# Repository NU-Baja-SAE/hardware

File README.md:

# NU Baja SAE — Hardware

KiCad schematics, PCB layouts, wiring harness designs, and BOM tooling for all NU Baja SAE electronics boards: the eCVT controller, the DAQ node, and the HUD node.

This guide assumes you have never used Git, GitHub, or KiCad before. Follow it top to bottom the first time; after that, skip to [Day-to-day workflow](#day-to-day-workflow).

## Table of contents

- [Glossary](#glossary)
- [One-time setup](#one-time-setup)
- [Getting the files onto your computer](#getting-the-files-onto-your-computer)
- [Opening a board in KiCad](#opening-a-board-in-kicad)
- [Day-to-day workflow](#day-to-day-workflow)
- [Structure](#structure)
- [Releases](#releases)
- [KiCad version](#kicad-version)

## Glossary

A few words you will see everywhere in this guide and on GitHub itself:

| Term | Meaning |
|---|---|
| Repository ("repo") | A folder of files (this one) tracked by Git, with full history of every change. |
| Git | The tool that tracks changes to files over time. Runs on your computer. |
| GitHub | The website that hosts a copy of the repo online so the team can share it. |
| Clone | Downloading a full copy of the repo (with its history) onto your computer. |
| Commit | A saved snapshot of your changes, with a short message describing what changed. |
| Push | Uploading your commits from your computer to GitHub. |
| Pull | Downloading other people's commits from GitHub to your computer. |
| Branch | An independent line of work, so you can make changes without touching `main` until they are ready. |
| Pull Request (PR) | A request to merge your branch into `main`, where others can review your changes before they land. |
| `main` | The default branch — the official, current state of the repo. |

## One-time setup

You only need to do this once per computer.

1. Create a GitHub account at [github.com](https://github.com) if you do not have one, and ask a team lead to add you to the `NU-Baja-SAE` organization so you have push access.
2. Install Git:
   - Windows: download and run the installer from [git-scm.com](https://git-scm.com/downloads). Default options are fine.
   - Mac: open Terminal and run `git --version` — macOS will offer to install it for you if it is missing.
3. Install GitHub Desktop (recommended if you are new to Git) from [desktop.github.com](https://desktop.github.com). It gives you a visual interface for the commit/push/pull steps below instead of typing commands. Everything in this guide can be done either with GitHub Desktop's buttons or with the `git` command line — both are described below.
4. Install KiCad — see [KiCad version](#kicad-version) below for which version to install. Download from [kicad.org/download](https://www.kicad.org/download/).
5. After cloning the repo (next section), add the shared parts library so connectors/ICs used across boards show up in KiCad — see [`libraries/README.md`](libraries/README.md).

## Getting the files onto your computer

This is called cloning the repo — it only needs to be done once per computer, after which you just "pull" updates.

Using GitHub Desktop:
1. Open GitHub Desktop and sign in with your GitHub account (File → Options → Accounts).
2. Click File → Clone Repository.
3. Choose the URL tab and paste: `https://github.com/NU-Baja-SAE/hardware`
4. Pick a local folder (e.g. `Documents/NU-Baja-SAE/hardware`) and click Clone.

Using the command line (Git Bash on Windows, Terminal on Mac):
```
git clone https://github.com/NU-Baja-SAE/hardware.git
cd hardware
```

Either way, you now have a folder called `hardware` on your computer containing everything in this repo.

## Opening a board in KiCad

Each board lives in its own folder under `boards/`, e.g. `boards/ecvt-controller/`. Inside that folder is a `.kicad_pro` file — this is the project file.

1. Open KiCad.
2. File → Open Project, then navigate to e.g. `hardware/boards/ecvt-controller/` and select the `.kicad_pro` file.
3. KiCad's project window shows the schematic (`.kicad_sch`) and PCB layout (`.kicad_pcb`) for that board — double-click either to open it in the schematic editor or PCB editor.
4. Make your edits and save (Ctrl+S / Cmd+S) as you normally would in KiCad. Saving only writes to your local copy of the files — it does not upload anything to GitHub. See the next section for how to share your changes.

If you are new to KiCad itself (not just this repo), the official [Getting Started guide](https://docs.kicad.org/) walks through schematic capture and PCB layout basics — worth a read before your first board edit.

## Day-to-day workflow

The general loop, every time you sit down to work on a board:

### 1. Pull the latest changes

Before you start editing, make sure you have everyone else's latest work, so you are not editing an outdated copy.

- GitHub Desktop: click Fetch origin, then Pull origin if it appears.
- Command line: `git pull`

### 2. Create a branch for your change

Do not edit `main` directly — work on a branch so your in-progress changes do not affect anyone else until they are reviewed.

- GitHub Desktop: click the branch dropdown (top middle) → New Branch. Name it something descriptive, e.g. `ecvt-add-current-sense`.
- Command line: `git checkout -b ecvt-add-current-sense`

### 3. Make your changes

Edit the KiCad files (schematic, PCB, etc.), or BOM/harness files, and save them as usual.

### 4. Commit your changes

A commit is a saved checkpoint with a message describing what you did. Commit often, in small logical chunks (e.g. "Add current sense resistor to eCVT controller" rather than one giant commit at the end).

- GitHub Desktop: the left panel lists every changed file. Check the ones you want to include, write a summary in the box at bottom-left, and click Commit to `<branch-name>`.
- Command line:
  ```
  git add boards/ecvt-controller/
  git commit -m "Add current sense resistor to eCVT controller"
  ```

### 5. Push your branch to GitHub

This uploads your commits so others (and CI, see below) can see them.

- GitHub Desktop: click Push origin.
- Command line: `git push -u origin ecvt-add-current-sense`

### 6. Open a Pull Request (PR)

A PR is how you propose merging your branch into `main`.

1. Go to [github.com/NU-Baja-SAE/hardware](https://github.com/NU-Baja-SAE/hardware) — GitHub usually shows a yellow banner offering to Compare & pull request for the branch you just pushed. Click it (or use GitHub Desktop's Create Pull Request button).
2. Write a short description of what changed and why.
3. Click Create pull request.
4. Automated checks (CI) will run against your PR — see `.github/workflows/ci.yml` for what gets checked (ERC/DRC, BOM diff, rendered schematic/PCB images, etc.). Wait for these to finish and fix anything they flag.
5. Ask a teammate to review. Once approved, click Merge pull request on GitHub.
6. Delete the branch (GitHub will prompt you) — its changes now live permanently in `main`.

### 7. Switch back to `main` and pull

- GitHub Desktop: switch the branch dropdown back to `main`, then Pull origin.
- Command line: `git checkout main && git pull`

You are back to a clean, up-to-date `main`, ready to start the loop again for your next change.

## Structure

```
hardware/
├── boards/
│   ├── ecvt-controller/   (.kicad_pro/.kicad_sch/.kicad_pcb + fab-outputs/ + README.md)
│   ├── daq-node/
│   └── hud-node/
├── harness/                # WireViz or WireLab YAML source + output/ (generated SVGs)
├── bom/
│   ├── consolidated-bom.csv
│   └── scripts/generate_bom.py
├── libraries/              # shared KiCad symbol/footprint libs
└── .github/workflows/
```

- `boards/<name>/` — one folder per physical board. Each contains its own KiCad project (`.kicad_pro`), schematic (`.kicad_sch`), PCB layout (`.kicad_pcb`), a `fab-outputs/` folder for generated gerbers/drill files/STEP models (not committed by hand — see below), and a short `README.md` describing the board.
- `harness/` — wiring harness definitions (WireViz/WireLab YAML), with rendered diagrams in `harness/output/`.
- `bom/` — the consolidated bill of materials across all boards (`consolidated-bom.csv`), generated automatically from the schematics by `bom/scripts/generate_bom.py`. Never edit the CSV by hand. If you change a schematic, run `python3 bom/scripts/generate_bom.py` and commit the updated CSV alongside your change — CI fails the PR if the committed CSV is out of date (and auto-regenerates it on direct pushes to `main` as a safety net).
- `libraries/` — shared KiCad symbol and footprint libraries used by more than one board, so parts stay consistent across designs.
- `.github/workflows/` — CI configuration; this is what automatically checks your PRs (see step 6 above).

Do not manually commit fab outputs (gerbers, drill files, `.step` files) — these are generated from the KiCad source files and are gitignored. CI regenerates them automatically on each PR.

## Releases

Board releases are tagged at the point gerbers are sent to fab, e.g. `ecvt-controller-v1.2`, with a one-line changelog per board.

## KiCad version

All board files must be authored/saved in the same KiCad version to avoid spurious diffs from format upgrades. Current standard version: **KiCad 10.0** — this is also the version CI runs (the `kicad/kicad:10.0` image in `.github/workflows/ci.yml`), so files saved in a newer major version will fail CI until both are bumped together.

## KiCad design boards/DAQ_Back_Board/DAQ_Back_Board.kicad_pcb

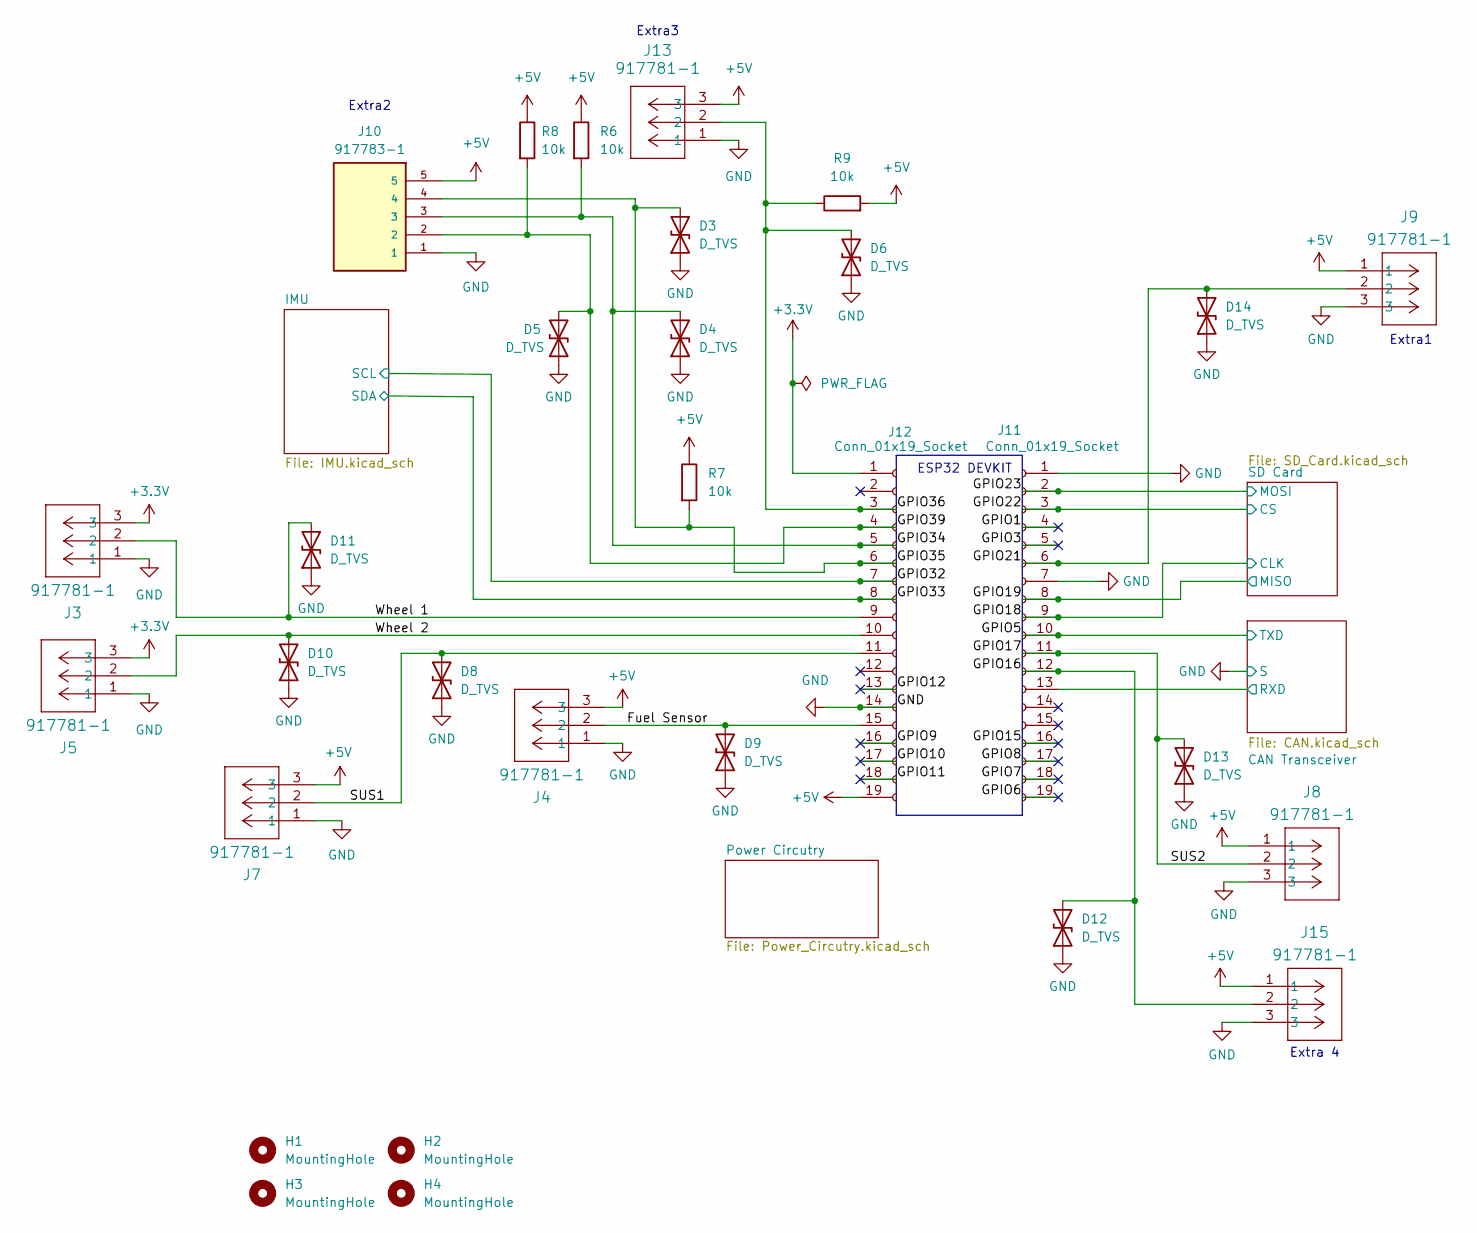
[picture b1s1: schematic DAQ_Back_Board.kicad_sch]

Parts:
D3, D4, D5, D6, D8, D9, D10, D11, D12, D13, D14: D_TVS; D_SOD-323_HandSoldering
H1, H2, H3, H4: MountingHole; MountingHole_3.2mm_M3
J3, J4, J5, J7, J8, J9, J13, J15: 917781-1; TE-Connectivity_917781
J10: 917783-1; Connector_1x5; PARTREV R
J11, J12: Conn_01x19_Socket; PinSocket_1x19_P2.54mm_Vertical
R6, R7, R8, R9: 10k; R_0603_1608Metric_Pad0.98x0.95mm_HandSolder

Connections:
+3.3V: J3.3, J5.3, J12.1; also elsewhere on the board
+5V: J4.3, J7.3, J8.1, J9.1, J10.5, J12.19, J13.3, J15.1, R6.1, R7.1, R8.1, R9.2; also elsewhere on the board
/CAN Transceiver/RXD: J11.13; also elsewhere on the board
/Fuel Sensor: D9.2 (A2), J4.2, J12.15
/GPIO1: J11.4
/GPIO3: J11.5
/GPIO5: J11.10; also elsewhere on the board
/GPIO6: J11.19
/GPIO7: J11.18
/GPIO8: J11.17
/GPIO9: J12.16
/GPIO10: J12.17
/GPIO11: J12.18
/GPIO12: J12.13
/GPIO15: J11.16
/GPIO16: D12.2 (A2), J11.12, J15.2
/GPIO17: D13.2 (A2), J8.2, J11.11
/GPIO18: J11.9; also elsewhere on the board
/GPIO19: J11.8; also elsewhere on the board
/GPIO21: D14.2 (A2), J9.2, J11.6
/GPIO22: J11.3; also elsewhere on the board
/GPIO23: J11.2; also elsewhere on the board
/GPIO32: J12.7; also elsewhere on the board
/GPIO33: J12.8; also elsewhere on the board
/GPIO34: D4.2 (A2), J10.3, J12.5, R6.2
/GPIO35: D3.2 (A2), J10.4, J12.6, R7.2
/GPIO36: D6.2 (A2), J12.3, J13.2, R9.1
/GPIO39: D5.2 (A2), J10.2, J12.4, R8.2
/SUS1: D8.2 (A2), J7.2, J12.11
/Wheel 1: D11.2 (A2), J3.2, J12.9
/Wheel 2: D10.2 (A2), J5.2, J12.10
GND: D3.1 (A1), D4.1 (A1), D5.1 (A1), D6.1 (A1), D8.1 (A1), D9.1 (A1), D10.1 (A1), D11.1 (A1), D12.1 (A1), D13.1 (A1), D14.1 (A1), J3.1, J4.1, J5.1, J7.1, J8.3, J9.3, J10.1, J11.1, J11.7, J12.14, J13.1, J15.3; also elsewhere on the board

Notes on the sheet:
ESP32 DEVKIT
Extra2
Extra1
Extra3
Extra 4

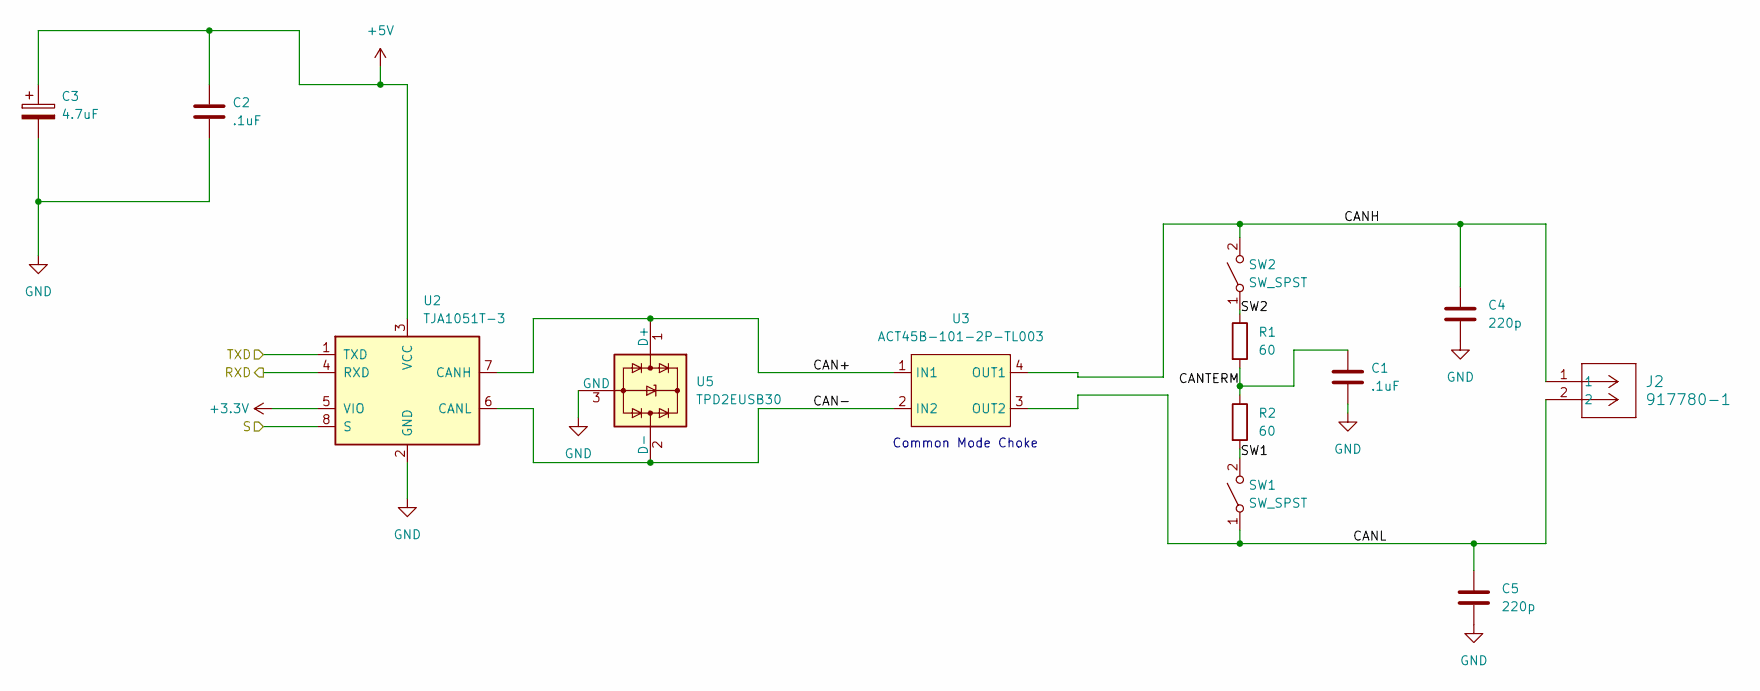
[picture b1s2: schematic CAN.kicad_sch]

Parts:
C1, C2: .1uF; C_0603_1608Metric_Pad1.08x0.95mm_HandSolder
C3: 4.7uF; C_0603_1608Metric_Pad1.08x0.95mm_HandSolder
C4, C5: 220p; C_0603_1608Metric_Pad1.08x0.95mm_HandSolder
J2: 917780-1; TE-Connectivity_ 917780
R1, R2: 60; R_1206_3216Metric_Pad1.30x1.75mm_HandSolder
SW1, SW2: SW_SPST; SW_DIP_SPSTx01_Slide_Copal_CHS-01A_W5.08mm_P1.27mm_JPin
U2: TJA1051T-3; SOIC-8_3.9x4.9mm_P1.27mm
U3: ACT45B-101-2P-TL003
U5: TPD2EUSB30; Texas_DRT-3

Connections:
+3.3V: U2.5 (VIO); also elsewhere on the board
+5V: C2.1, C3.1, U2.3 (VCC); also elsewhere on the board
/CAN Transceiver/CAN+: U2.7 (CANH), U3.1 (IN1), U5.1 (D+)
/CAN Transceiver/CAN-: U2.6 (CANL), U3.2 (IN2), U5.2 (D-)
/CAN Transceiver/CANH: C4.1, J2.1, SW2.2 (B), U3.4 (OUT1)
/CAN Transceiver/CANL: C5.1, J2.2, SW1.1 (A), U3.3 (OUT2)
/CAN Transceiver/CANTERM: C1.1, R1.2, R2.1
/CAN Transceiver/RXD: U2.4 (RXD); also elsewhere on the board
/CAN Transceiver/SW1: R2.2, SW1.2 (B)
/CAN Transceiver/SW2: R1.1, SW2.1 (A)
/GPIO5: U2.1 (TXD); also elsewhere on the board
GND: C1.2, C2.2, C3.2, C4.2, C5.2, U2.2 (GND), U2.8 (S), U5.3 (GND); also elsewhere on the board

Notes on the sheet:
Common Mode Choke

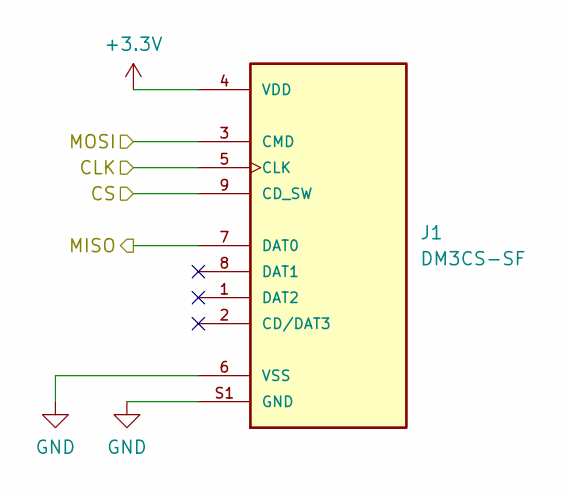
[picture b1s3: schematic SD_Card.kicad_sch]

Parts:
J1: DM3CS-SF; SD_Card; PARTREV n/a

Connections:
+3.3V: J1.4 (VDD); also elsewhere on the board
/GPIO18: J1.5 (CLK); also elsewhere on the board
/GPIO19: J1.7 (DAT0); also elsewhere on the board
/GPIO22: J1.9 (CD_SW); also elsewhere on the board
/GPIO23: J1.3 (CMD); also elsewhere on the board
GND: J1.6 (VSS), J1.S1 (GND), J1.S2 (GND), J1.S3 (GND), J1.S5 (GND); also elsewhere on the board

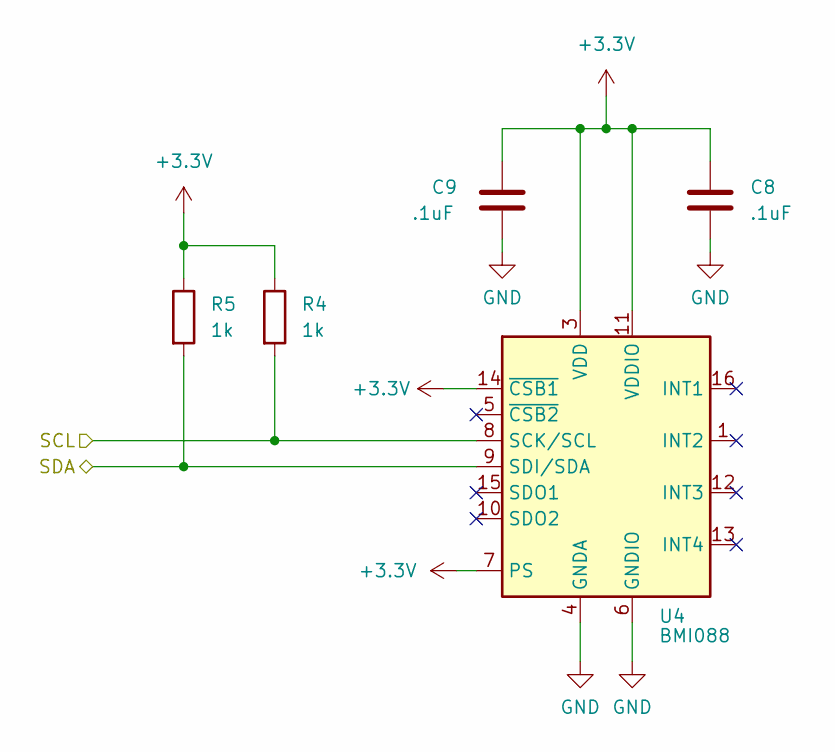
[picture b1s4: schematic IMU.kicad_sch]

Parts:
C8, C9: .1uF; C_0603_1608Metric_Pad1.08x0.95mm_HandSolder
R4, R5: 1k; R_0603_1608Metric_Pad0.98x0.95mm_HandSolder
U4: BMI088; Bosch_LGA-16_4.5x3mm_P0.5mm_LayoutBorder7x1y_ClockwisePinNu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

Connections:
+3.3V: C8.1, C9.1, R4.1, R5.1, U4.3 (VDD), U4.7 (PS), U4.11 (VDDIO), U4.14 (~CSB1); also elsewhere on the board
/GPIO32: R4.2, U4.8 (SCK/SCL); also elsewhere on the board
/GPIO33: R5.2, U4.9 (SDI/SDA); also elsewhere on the board
GND: C8.2, C9.2, U4.2 (GNDA), U4.4 (GNDA), U4.6 (GNDIO); also elsewhere on the board

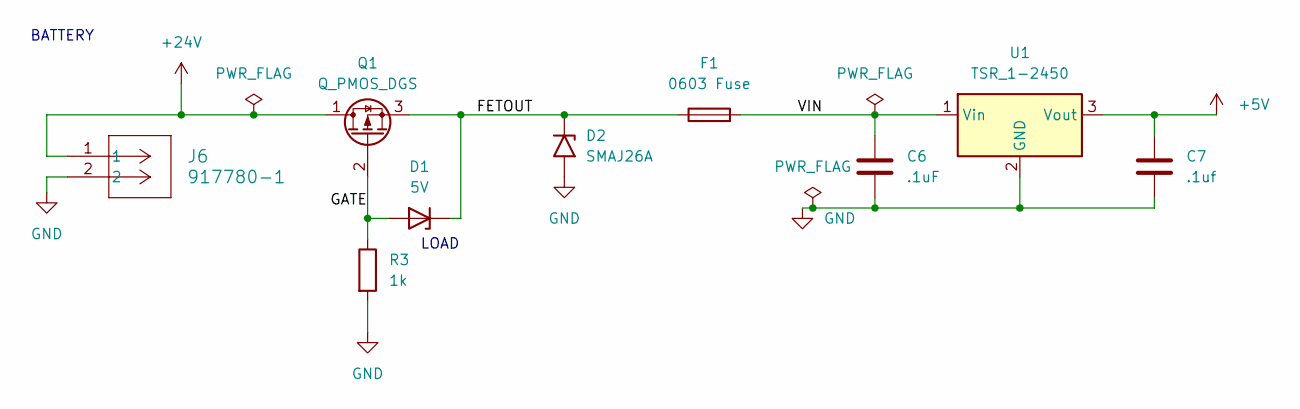
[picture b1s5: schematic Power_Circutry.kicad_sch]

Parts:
C6: .1uF; C_0603_1608Metric_Pad1.08x0.95mm_HandSolder
C7: .1uf; C_0603_1608Metric_Pad1.08x0.95mm_HandSolder
D1: 5V; D_SMA
D2: SMAJ26A; D_SMA
F1: 0603 Fuse; Fuse_0603_1608Metric_Pad1.05x0.95mm_HandSolder
J6: 917780-1; TE-Connectivity_ 917780
Q1: Q_PMOS_DGS; SOT-23-3
R3: 1k; R_0603_1608Metric_Pad0.98x0.95mm_HandSolder
U1: TSR_1-2450; Converter_DCDC_TRACO_TSR-1_THT

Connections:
+5V: C7.1, U1.3 (Vout); also elsewhere on the board
+24V: J6.1, Q1.1 (D)
/Power Circutry/FETOUT: D1.1 (K), D2.1 (A1), F1.1, Q1.3 (S)
/Power Circutry/GATE: D1.2 (A), Q1.2 (G), R3.1
/Power Circutry/VIN: C6.1, F1.2, U1.1 (Vin)
GND: C6.2, C7.2, D2.2 (A2), J6.2, R3.2, U1.2 (GND); also elsewhere on the board

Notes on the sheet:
LOAD
BATTERY

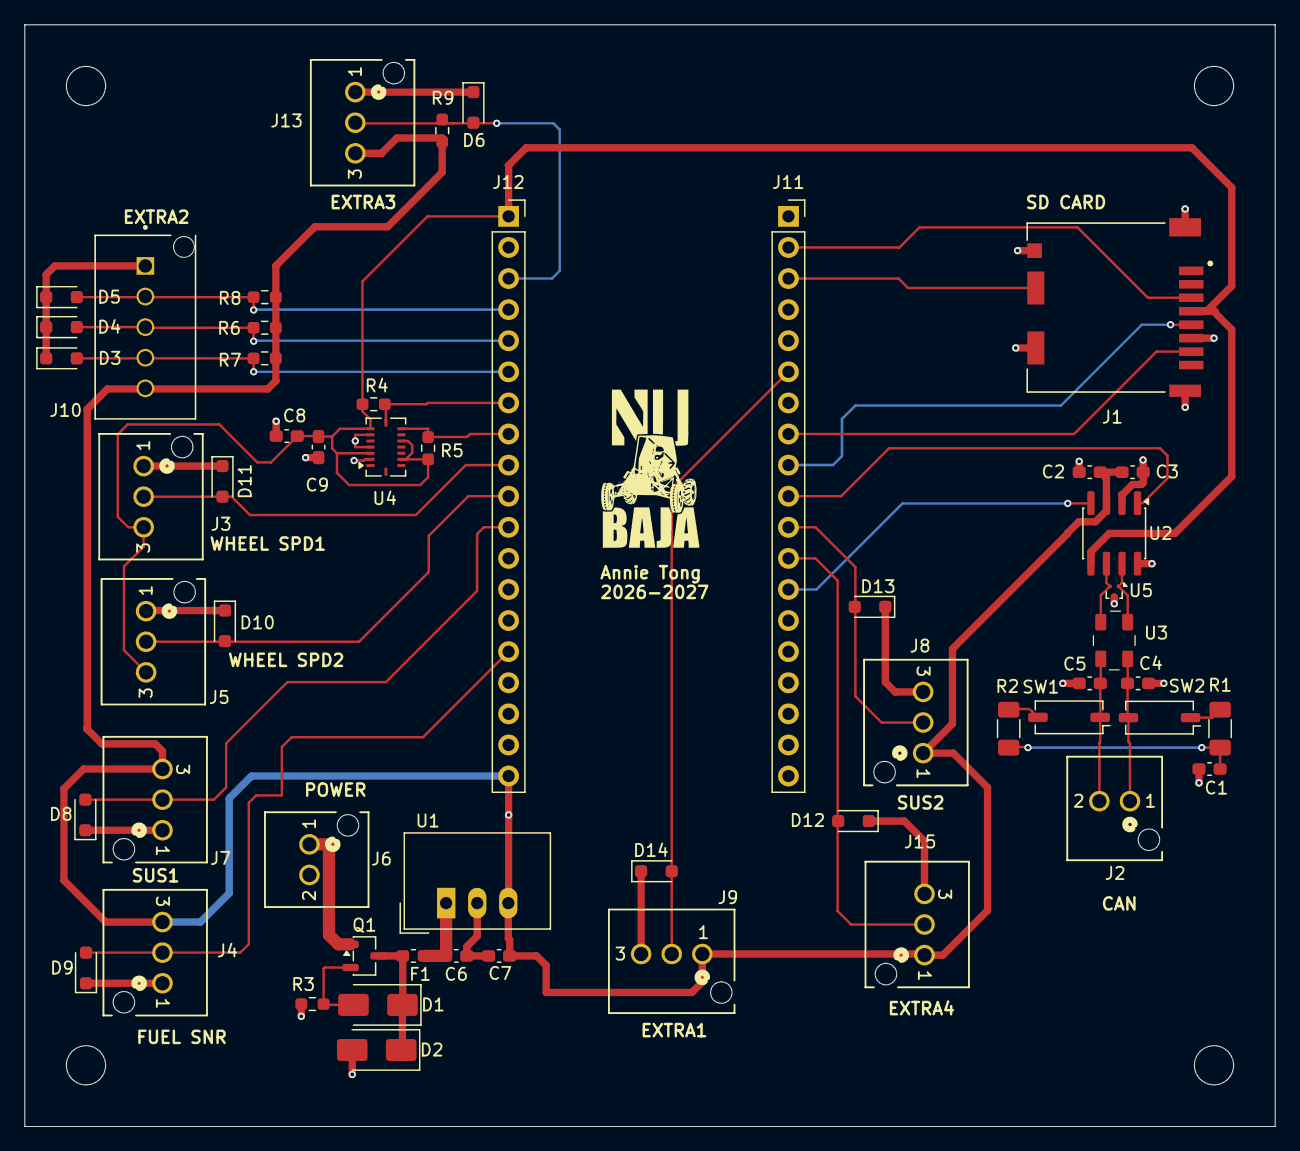
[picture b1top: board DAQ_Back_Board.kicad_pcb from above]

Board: 4 copper layers, 102.2 x 90.0 mm, 58 parts (0 on the bottom side), 33 nets.

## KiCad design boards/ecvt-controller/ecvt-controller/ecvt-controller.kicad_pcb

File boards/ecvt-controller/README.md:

# ecvt-controller

KiCad project for the eCVT controller board. Add `.kicad_pro`/`.kicad_sch`/`.kicad_pcb` files here, with generated fab outputs under `fab-outputs/` (gitignored).

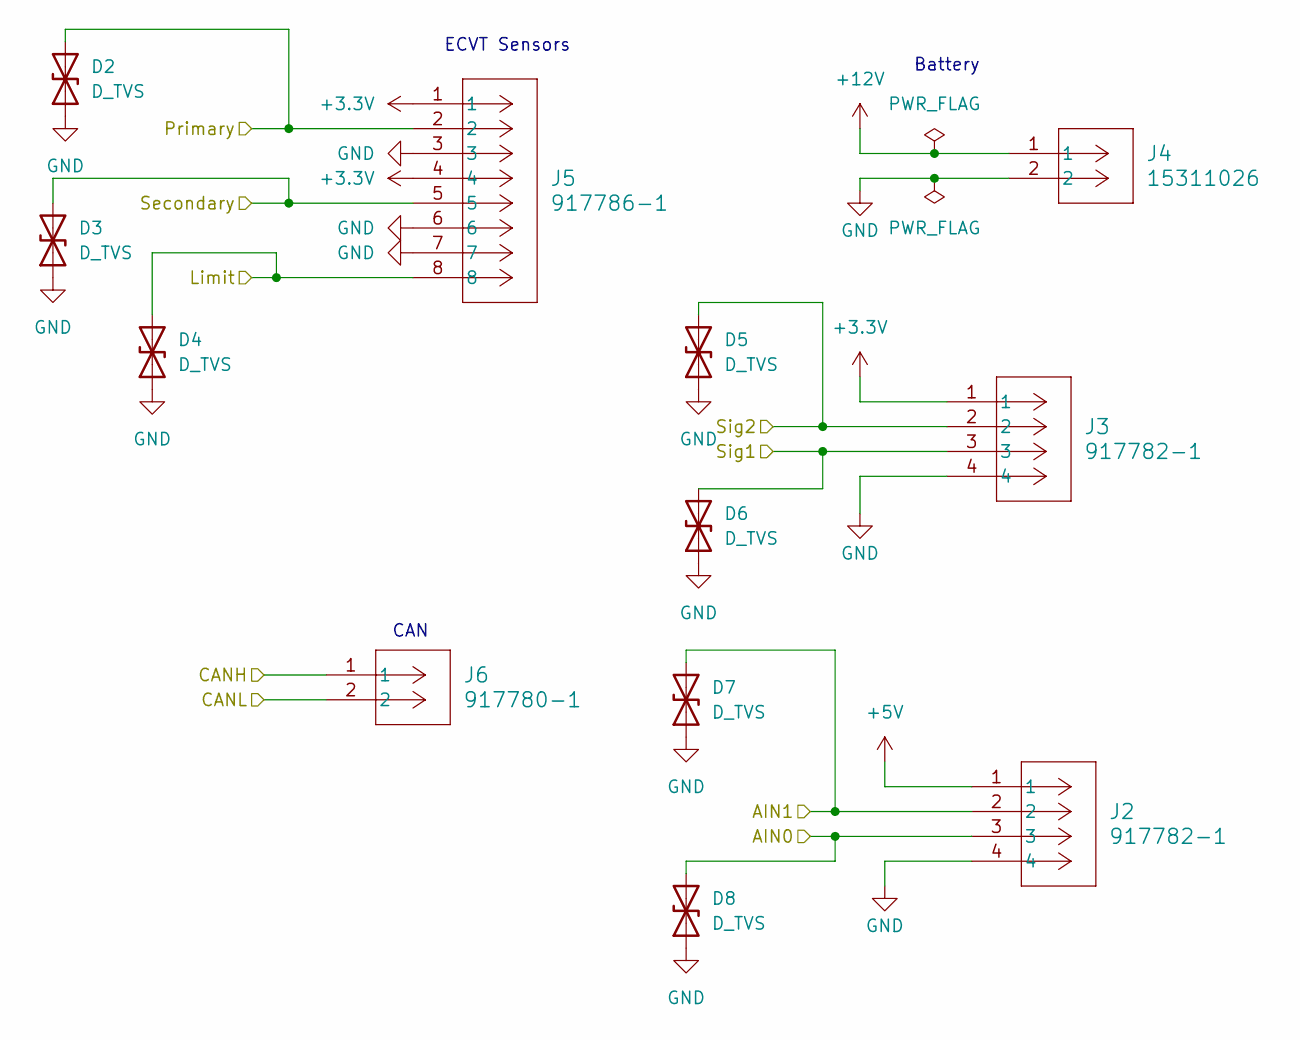
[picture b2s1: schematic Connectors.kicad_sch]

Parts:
D2, D3, D4, D5, D6, D7, D8: D_TVS; D_SOD-323_HandSoldering
J2, J3: 917782-1; CON4_1X4_P100
J4: 15311026; MOLEX_15311026
J5: 917786-1; TE-Connectivity_917786
J6: 917780-1; TE-Connectivity_ 917780

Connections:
+5V: J2.1; also elsewhere on the board
+12V: J4.1; also elsewhere on the board
/ADC/AIN0: D8.2 (A2), J2.3; also elsewhere on the board
/ADC/AIN1: D7.2 (A2), J2.2; also elsewhere on the board
/CAN/CANH: J6.1; also elsewhere on the board
/CAN/CANL: J6.2; also elsewhere on the board
/Connectors/Limit: D4.2 (A2), J5.8; also elsewhere on the board
/Connectors/Primary: D2.2 (A2), J5.2; also elsewhere on the board
/Connectors/Secondary: D3.2 (A2), J5.5; also elsewhere on the board
/Connectors/Sig1: D6.2 (A2), J3.3; also elsewhere on the board
/Connectors/Sig2: D5.2 (A2), J3.2; also elsewhere on the board
GND: D2.1 (A1), D3.1 (A1), D4.1 (A1), D5.1 (A1), D6.1 (A1), D7.1 (A1), D8.1 (A1), J2.4, J3.4, J4.2, J5.3, J5.6, J5.7; also elsewhere on the board

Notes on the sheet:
ECVT Sensors
CAN
Battery

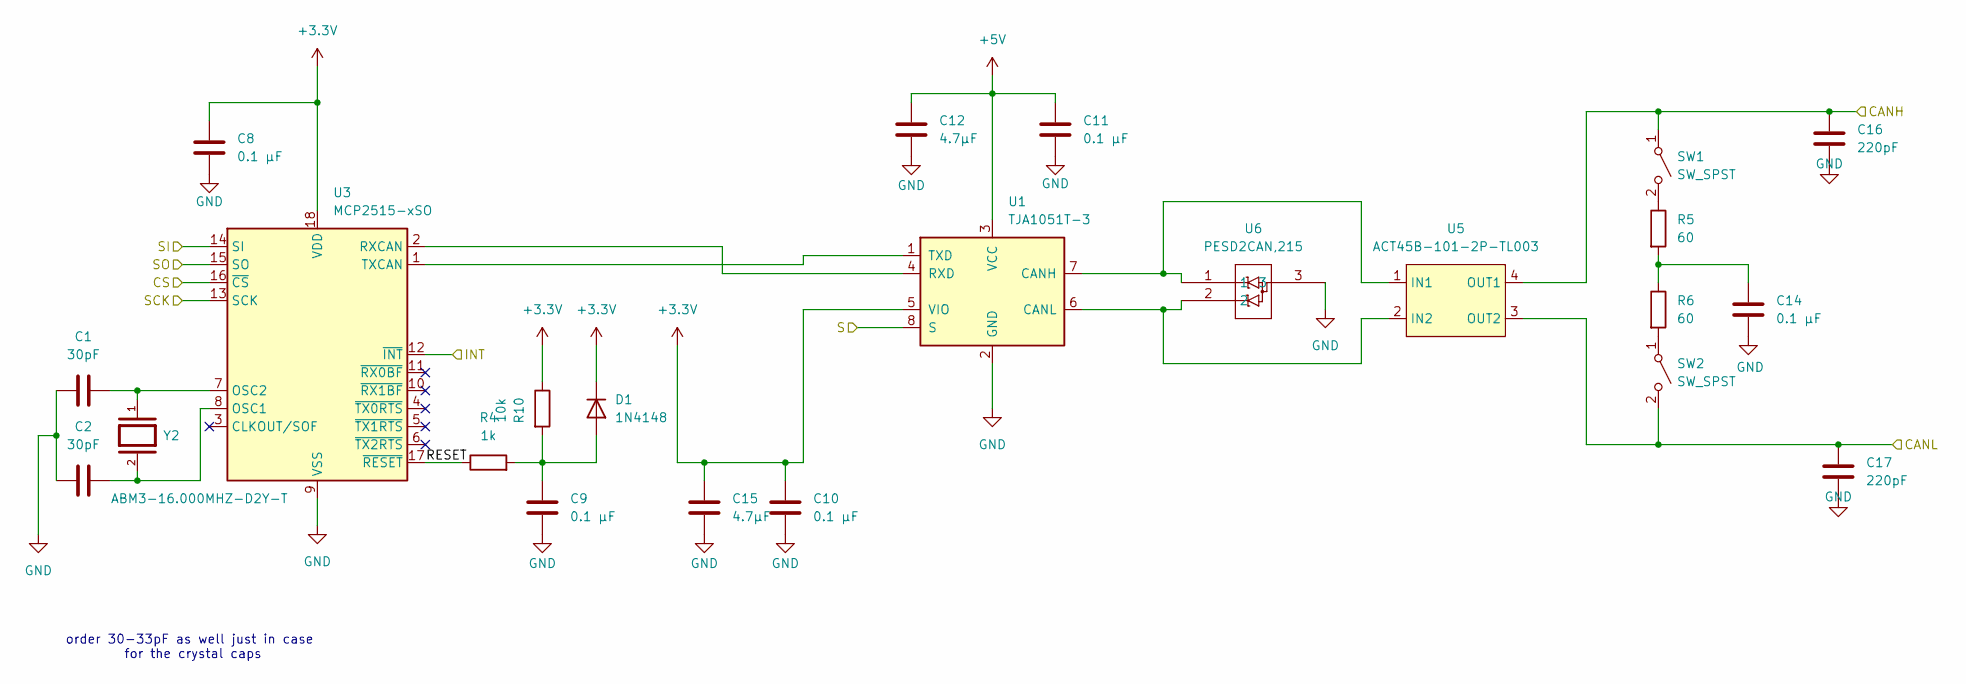
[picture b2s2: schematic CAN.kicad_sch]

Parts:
C1, C2: 30pF; C_0603_1608Metric_Pad1.08x0.95mm_HandSolder
C8, C9, C10, C11, C14: 0.1 µF; C_0603_1608Metric_Pad1.08x0.95mm_HandSolder
C12, C15: 4.7µF; C_0805_2012Metric_Pad1.18x1.45mm_HandSolder
C16, C17: 220pF; C_0603_1608Metric_Pad1.08x0.95mm_HandSolder
D1: 1N4148; D_DO-35_SOD27_P7.62mm_Horizontal
R4: 1k; R_0805_2012Metric_Pad1.20x1.40mm_HandSolder
R5, R6: 60; R_0603_1608Metric_Pad0.98x0.95mm_HandSolder
R10: 10k; R_0603_1608Metric_Pad0.98x0.95mm_HandSolder
SW1, SW2: SW_SPST; SW_DIP_SPSTx01_Slide_9.78x4.72mm_W7.62mm_P2.54mm
U1: TJA1051T-3; SOIC-8_3.9x4.9mm_P1.27mm
U3: MCP2515-xSO; SOIC-18W_7.5x11.6mm_P1.27mm
U5: ACT45B-101-2P-TL003
U6: PESD2CAN,215; SOT-23-3
Y2: ABM3-16.000MHZ-D2Y-T; XTAL_ABM3-16.000MHZ-D2Y-T; PARTREV 4/25/2022; DigiKey_Part_Number 535-10638-1-ND

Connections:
+5V: C11.1, C12.1, U1.3 (VCC); also elsewhere on the board
/CAN/CANH: C16.1, SW1.1 (A), U5.4 (OUT1); also elsewhere on the board
/CAN/CANL: C17.1, SW2.2 (B), U5.3 (OUT2); also elsewhere on the board
/CAN/CS: U3.16 (~CS); also elsewhere on the board
/CAN/INT: U3.12 (~INT); also elsewhere on the board
/CAN/RESET: R4.1, U3.17 (~RESET)
/CAN/SCK: U3.13 (SCK); also elsewhere on the board
/CAN/SI: U3.14 (SI); also elsewhere on the board
/CAN/SO: U3.15 (SO); also elsewhere on the board
GND: C1.1, C2.1, C8.2, C9.2, C10.2, C11.2, C12.2, C14.2, C15.2, C16.2, C17.2, U1.2 (GND), U1.8 (S), U3.9 (VSS), U6.3; also elsewhere on the board
unnamed: C14.1, R5.2, R6.1
unnamed: C9.1, D1.2 (A), R4.2, R10.2
unnamed: R5.1, SW1.2 (B)
unnamed: R6.2, SW2.1 (A)
unnamed: U1.7 (CANH), U5.1 (IN1), U6.1
unnamed: U1.6 (CANL), U5.2 (IN2), U6.2
unnamed: U1.4 (RXD), U3.2 (RXCAN)
unnamed: U1.1 (TXD), U3.1 (TXCAN)
unnamed: C2.2, U3.8 (OSC1), Y2.2
unnamed: C1.2, U3.7 (OSC2), Y2.1

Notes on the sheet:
order 30-33pF as well just in case for the crystal caps

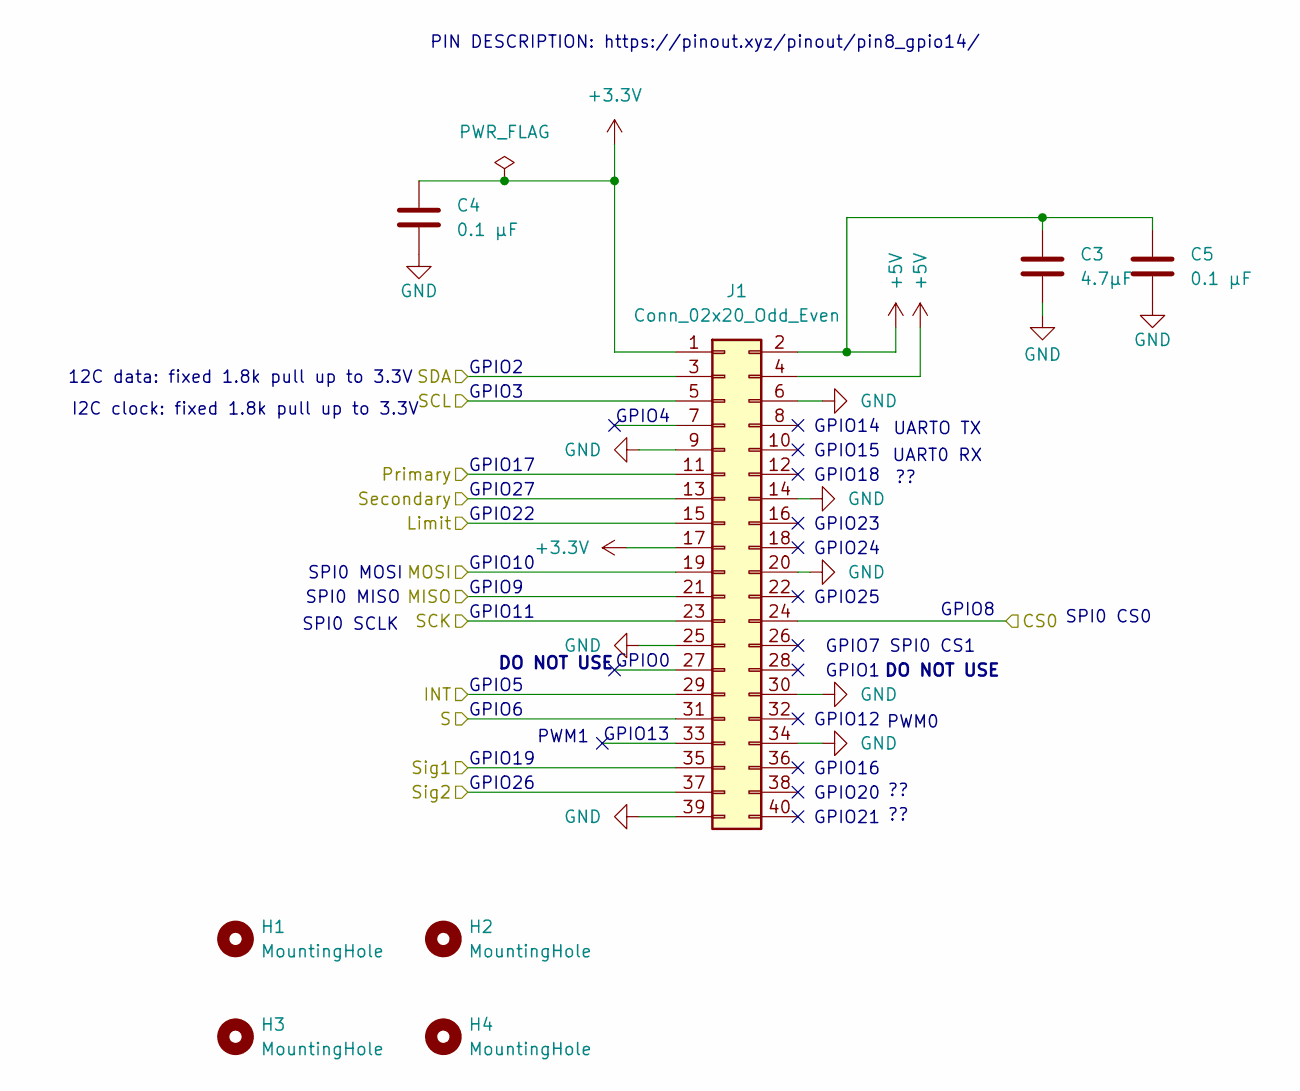
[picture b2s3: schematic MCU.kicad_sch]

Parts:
C3: 4.7µF; C_0805_2012Metric_Pad1.18x1.45mm_HandSolder
C4, C5: 0.1 µF; C_0603_1608Metric_Pad1.08x0.95mm_HandSolder
H1, H2, H3, H4: MountingHole; MountingHole_2.7mm_M2.5
J1: Conn_02x20_Odd_Even; PinSocket_2x20_P2.54mm_Vertical

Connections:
+5V: C3.1, C5.1, J1.2, J1.4; also elsewhere on the board
/ADC/SCL: J1.5; also elsewhere on the board
/ADC/SDA: J1.3; also elsewhere on the board
/CAN/CS: J1.24; also elsewhere on the board
/CAN/INT: J1.29; also elsewhere on the board
/CAN/SCK: J1.23; also elsewhere on the board
/CAN/SI: J1.19; also elsewhere on the board
/CAN/SO: J1.21; also elsewhere on the board
/Connectors/Limit: J1.15; also elsewhere on the board
/Connectors/Primary: J1.11; also elsewhere on the board
/Connectors/Secondary: J1.13; also elsewhere on the board
/Connectors/Sig1: J1.35; also elsewhere on the board
/Connectors/Sig2: J1.37; also elsewhere on the board
GND: C3.2, C4.2, C5.2, J1.6, J1.9, J1.14, J1.20, J1.25, J1.30, J1.34, J1.39; also elsewhere on the board

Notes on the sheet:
PWM0
GPIO7
GPIO12
GPIO21
GPIO22
GPIO6
PWM1
GPIO4
UART0 RX
I2C clock: fixed 1.8k pull up to 3.3V
GPIO18
GPIO3
GPIO25
DO NOT USE
GPIO1
GPIO10
GPIO8
PIN DESCRIPTION: https://pinout.xyz/pinout/pin8_gpio14/
GPIO26
GPIO20
12C data: fixed 1.8k pull up to 3.3V
GPIO15
SPI0 CS0
GPIO14
SPI0 MISO
GPIO27
GPIO9
GPIO2
GPIO5
GPIO23
GPIO19
SPI0 CS1
SPI0 SCLK
GPIO13
GPIO24
UARTO TX
GPIO17
SPI0 MOSI
GPIO0
GPIO16

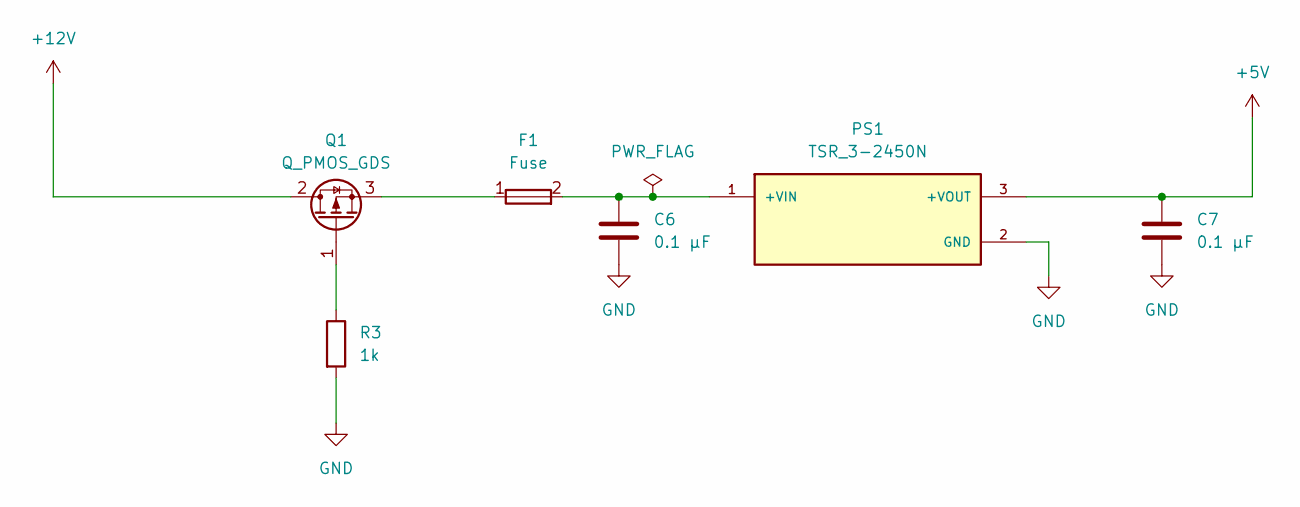
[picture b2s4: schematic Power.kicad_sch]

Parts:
C6, C7: 0.1 µF; C_0603_1608Metric_Pad1.08x0.95mm_HandSolder
F1: Fuse; Fuse_1206_3216Metric_Pad1.42x1.75mm_HandSolder
PS1: TSR_3-2450N; CONV_TSR_3-2450N; PARTREV December 18, 2024; DigiKey_Part_Number 1951-TSR3-2450N-ND
Q1: Q_PMOS_GDS; TO-252-2
R3: 1k; R_0805_2012Metric_Pad1.20x1.40mm_HandSolder

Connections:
+5V: C7.1, PS1.3 (+VOUT); also elsewhere on the board
+12V: Q1.2 (D); also elsewhere on the board
GND: C6.2, C7.2, PS1.2 (GND), R3.2; also elsewhere on the board
unnamed: C6.1, F1.2, PS1.1 (+VIN)
unnamed: Q1.1 (G), R3.1
unnamed: F1.1, Q1.3 (S)

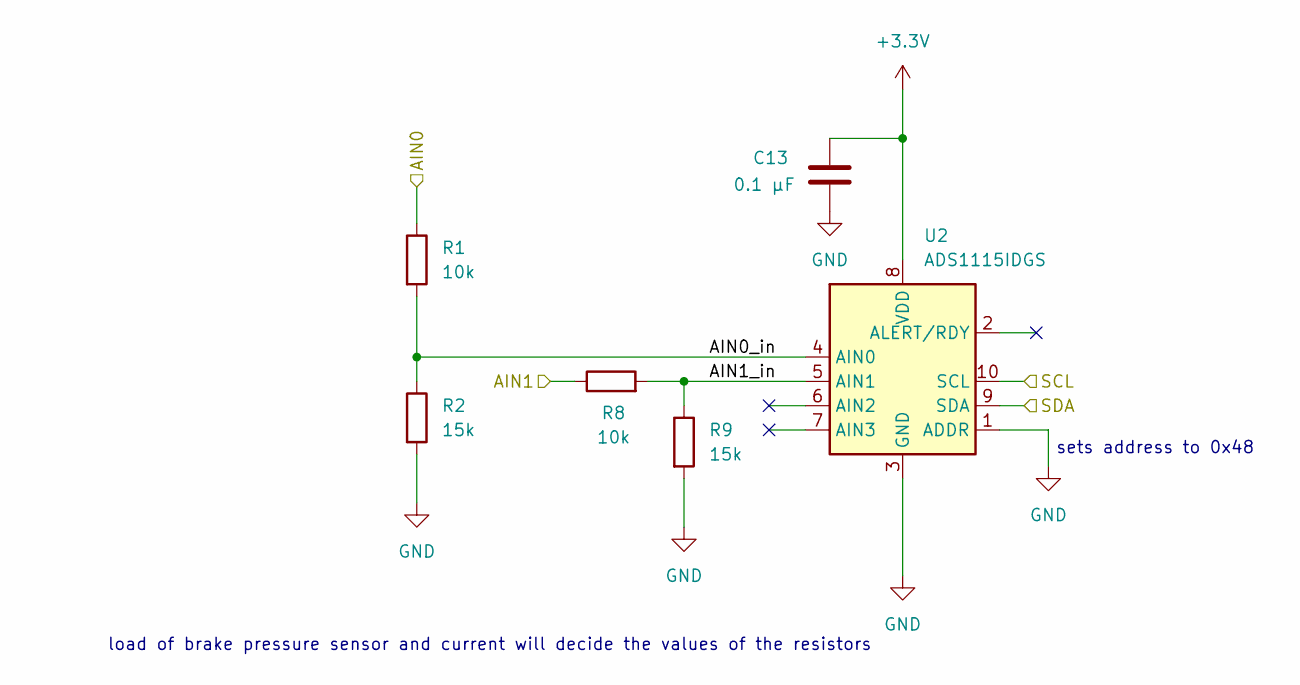
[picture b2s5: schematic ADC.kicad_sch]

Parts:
C13: 0.1 µF; C_0603_1608Metric_Pad1.08x0.95mm_HandSolder
R1, R8: 10k; R_0603_1608Metric_Pad0.98x0.95mm_HandSolder
R2, R9: 15k; R_0603_1608Metric_Pad0.98x0.95mm_HandSolder
U2: ADS1115IDGS; TSSOP-10_3x3mm_P0.5mm

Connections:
/ADC/AIN0: R1.1; also elsewhere on the board
/ADC/AIN0_in: R1.2, R2.1, U2.4 (AIN0)
/ADC/AIN1: R8.1; also elsewhere on the board
/ADC/AIN1_in: R8.2, R9.1, U2.5 (AIN1)
/ADC/SCL: U2.10 (SCL); also elsewhere on the board
/ADC/SDA: U2.9 (SDA); also elsewhere on the board
GND: C13.2, R2.2, R9.2, U2.1 (ADDR), U2.3 (GND); also elsewhere on the board

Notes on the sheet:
load of brake pressure sensor and current will decide the values of the resistors
sets address to 0x48

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
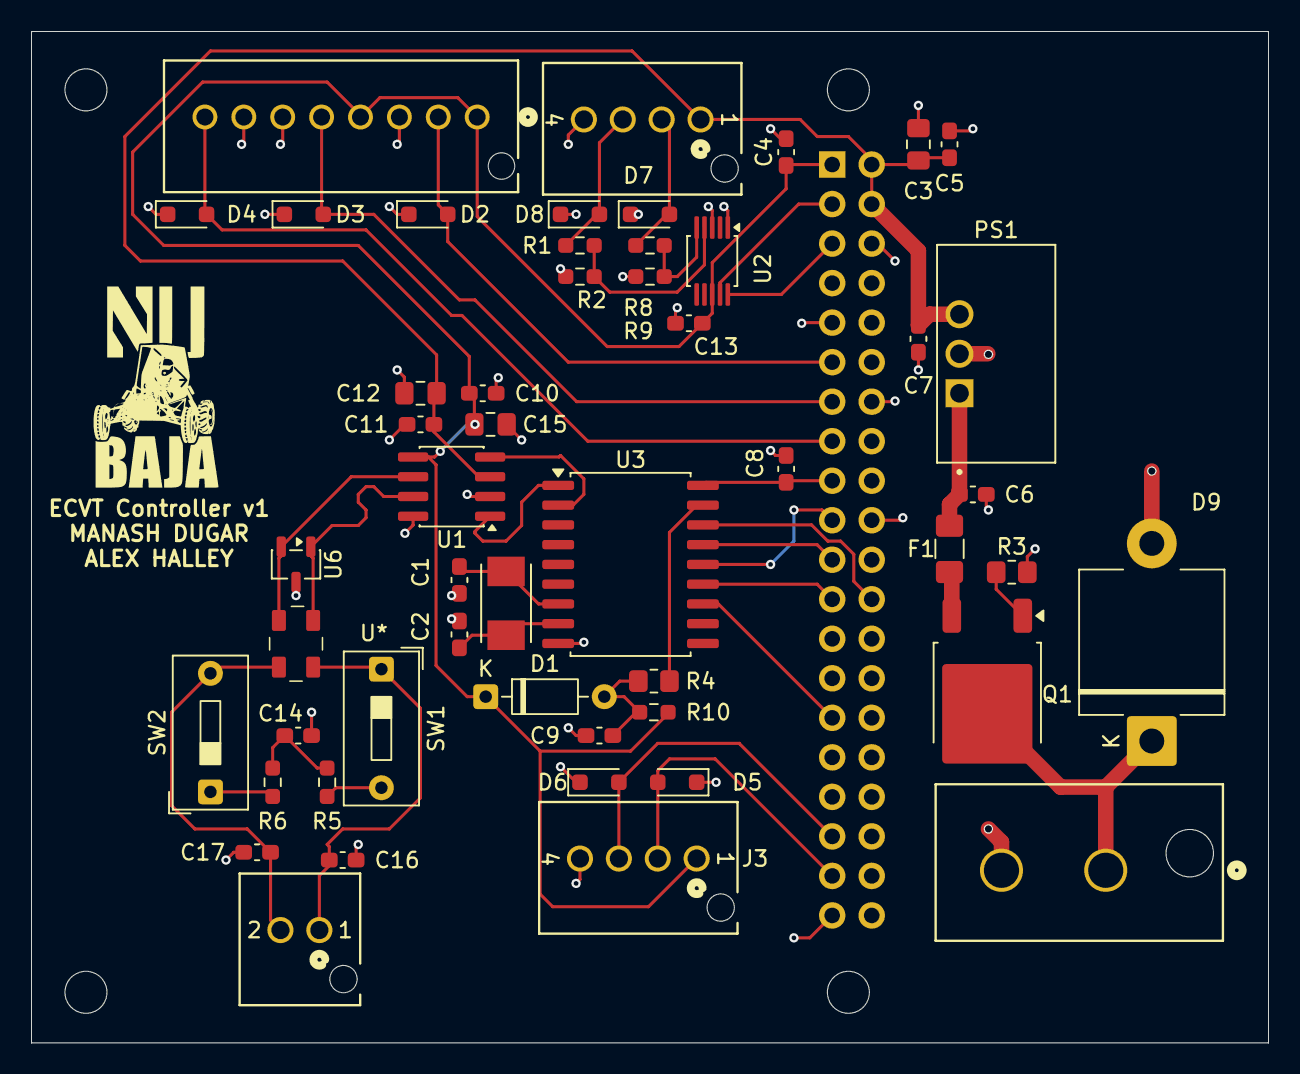
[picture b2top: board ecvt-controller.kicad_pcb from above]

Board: 2 copper layers, 79.5 x 65.0 mm, 56 parts (1 on the bottom side), 37 nets.

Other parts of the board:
D9: D_Zener; D_P600_R-6_P12.70mm_Horizontal

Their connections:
+12V: D9.1 (K); also elsewhere on the board
GND: D9.2 (A); also elsewhere on the board
